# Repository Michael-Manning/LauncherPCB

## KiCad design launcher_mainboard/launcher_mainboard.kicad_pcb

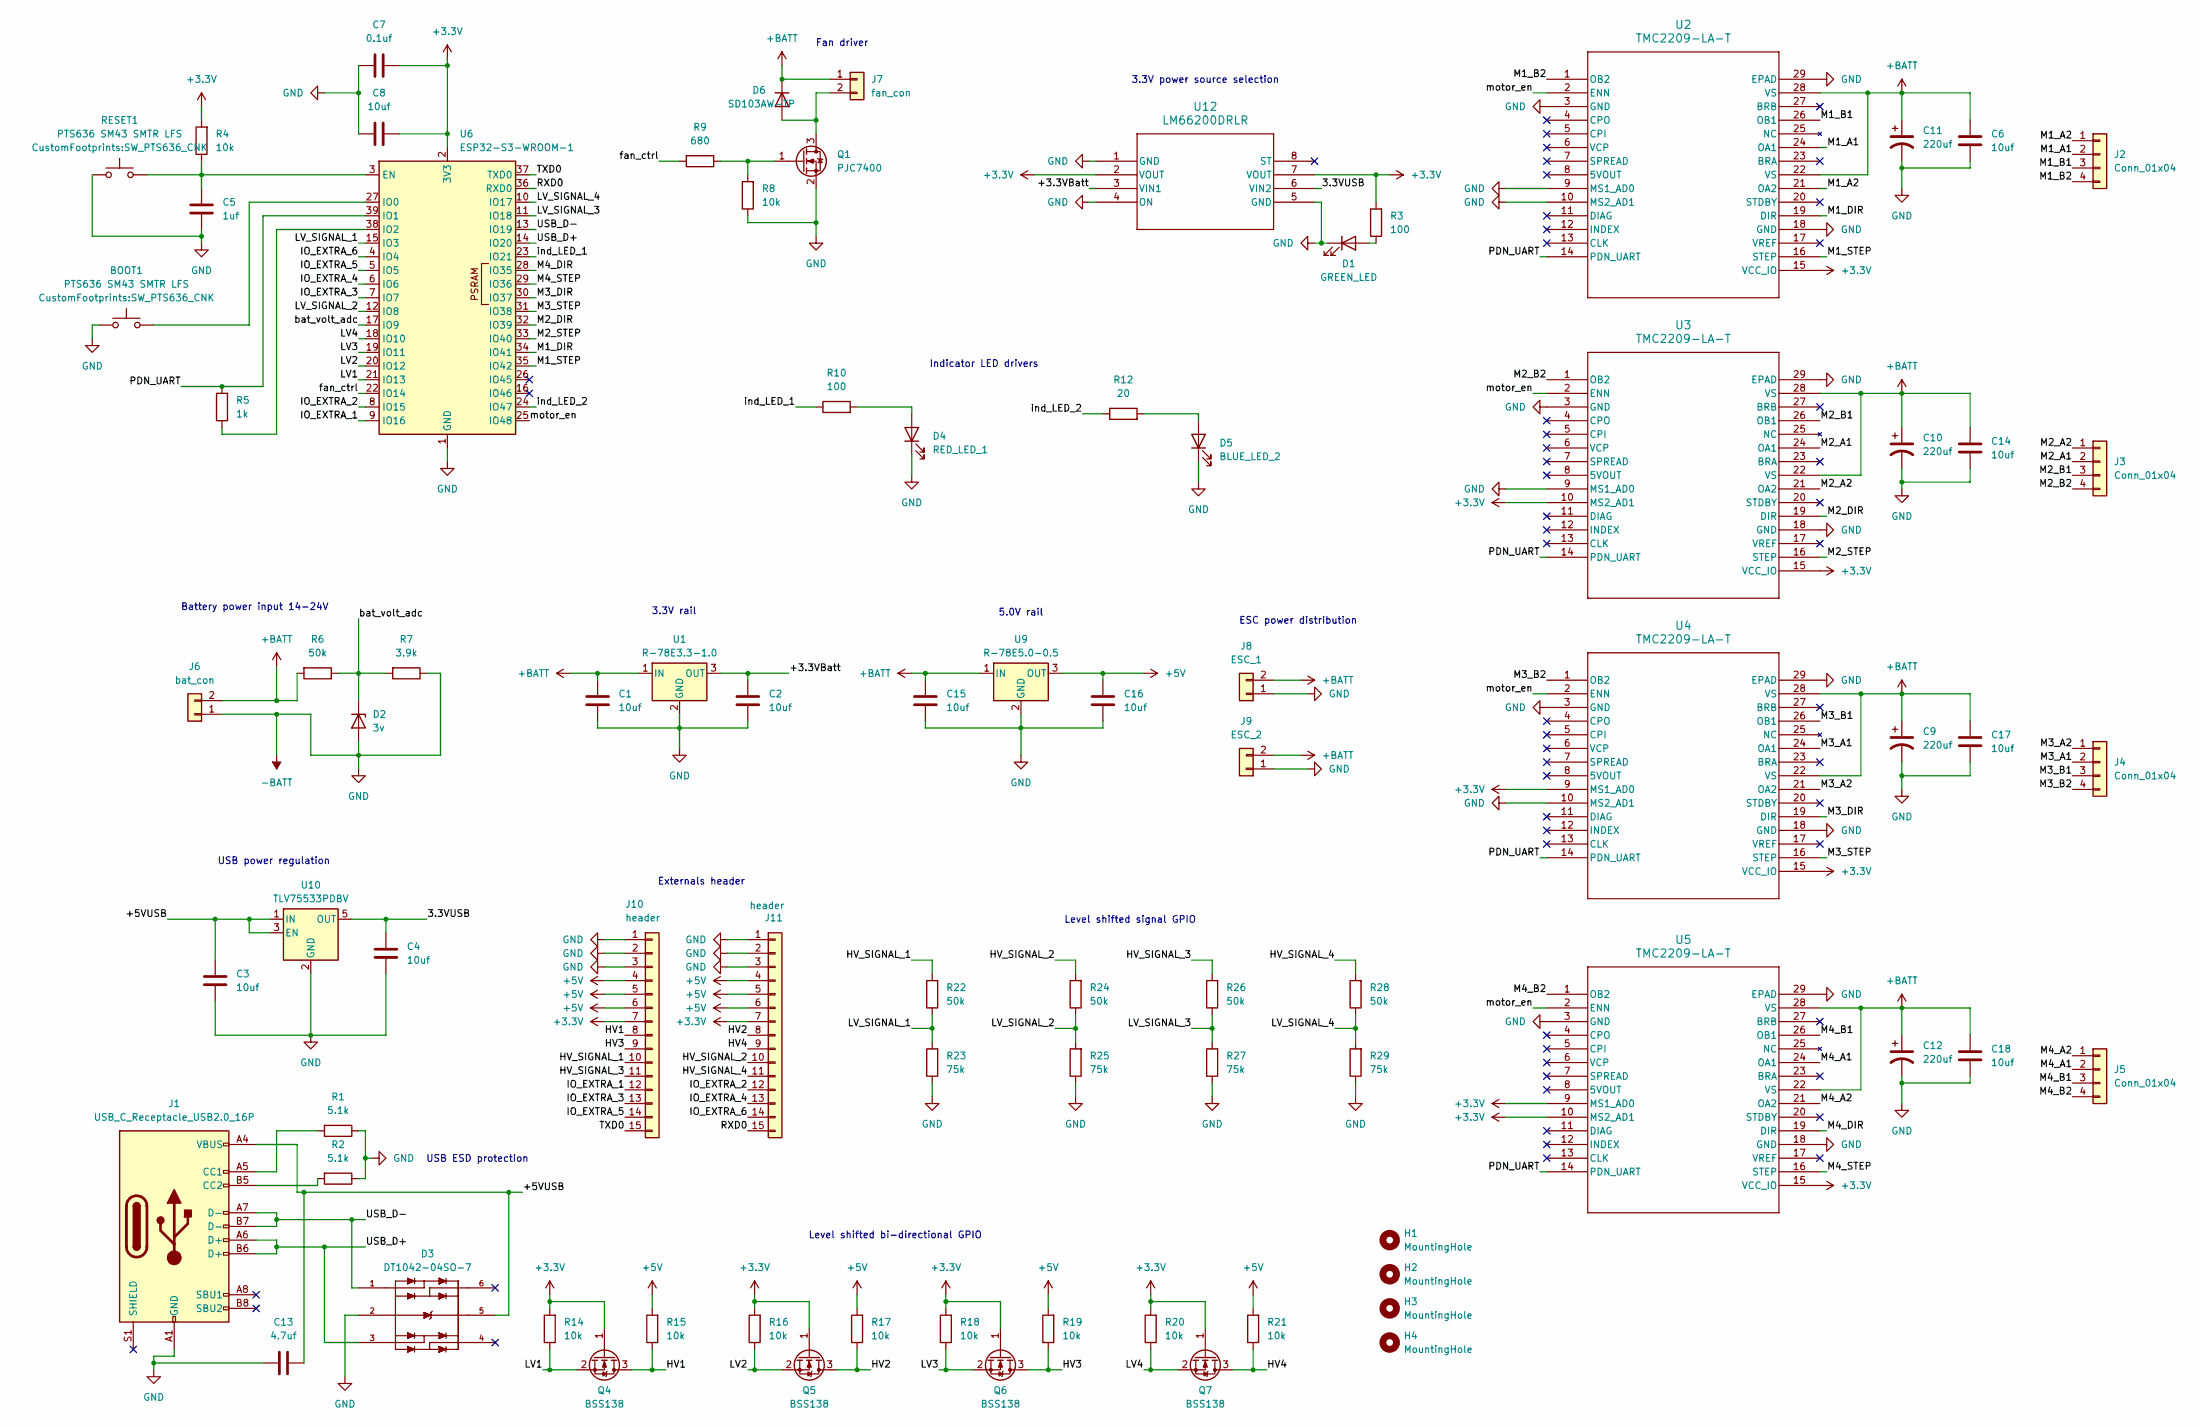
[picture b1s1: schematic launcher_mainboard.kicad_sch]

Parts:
BOOT1: PTS636 SM43 SMTR LFS; SW_PTS636_CNK
C1, C2, C3, C4, C6, C8, C14, C15, C16, C17, C18: 10uf; C_0805_2012Metric
C5: 1uf; C_0805_2012Metric
C7: 0.1uf; C_0805_2012Metric
C9, C10, C11, C12: 220uf; CP_Elec_8x6.7
C13: 4.7uf; C_0805_2012Metric
D1: GREEN_LED; LED_0805_2012Metric
D2: 3v; D_SOD-123
D3: DT1042-04SO-7; SOT95P285X140-6N; PARTREV 2-2
D4: RED_LED_1; LED_0805_2012Metric
D5: BLUE_LED_2; LED_0805_2012Metric
D6: SD103AW-TP; D_SOD-123
H1, H2, H3, H4: MountingHole; MountingHole_3.2mm_M3_Pad_TopBottom
J1: USB_C_Receptacle_USB2.0_16P; USB_C_Receptacle_GCT_USB4105-xx-A_16P_TopMnt_Horizontal
J2, J3, J4, J5: Conn_01x04; JST_XH_B4B-XH-A_1x04_P2.50mm_Vertical
J6: bat_con; AMASS_XT60-M_1x02_P7.20mm_Vertical
J7: fan_con; JST_XH_B2B-XH-A_1x02_P2.50mm_Vertical
J8: ESC_1; AMASS_XT60-F_1x02_P7.20mm_Vertical
J9: ESC_2; AMASS_XT60-F_1x02_P7.20mm_Vertical
J10, J11: header; PinHeader_1x15_P2.54mm_Vertical
Q1: PJC7400; SOT-323_SC-70
Q4, Q5, Q6, Q7: BSS138; SOT-23
R1, R2: 5.1k; R_0805_2012Metric
R3, R10: 100; R_0805_2012Metric
R4, R8, R14, R15, R16, R17, R18, R19, R20, R21: 10k; R_0805_2012Metric
R5: 1k; R_0805_2012Metric
R6, R22, R24, R26, R28: 50k; R_0805_2012Metric
R7: 3.9k; R_0805_2012Metric
R9: 680; R_0805_2012Metric
R12: 20; R_0805_2012Metric
R23, R25, R27, R29: 75k; R_0805_2012Metric
RESET1: PTS636 SM43 SMTR LFS; SW_PTS636_CNK
U1: R-78E3.3-1.0; Converter_DCDC_RECOM_R-78E-0.5_THT
U2, U3, U4, U5: TMC2209-LA-T; TCM2209_Module
U6: ESP32-S3-WROOM-1
U9: R-78E5.0-0.5; Converter_DCDC_RECOM_R-78E-0.5_THT
U10: TLV75533PDBV; SOT-23-5
U12: LM66200DRLR; SOT-5X3_DRL_TEX

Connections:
+3.3V: C7.2, C8.2, J10.7, J11.7, Q4.1 (G), Q5.1 (G), Q6.1 (G), Q7.1 (G), R3.2, R4.2, R14.2, R16.2, R18.2, R20.2, U2.15 (VCC_IO), U3.10 (MS2_AD1), U3.15 (VCC_IO), U4.9 (MS1_AD0), U4.15 (VCC_IO), U5.9 (MS1_AD0), U5.10 (MS2_AD1), U5.15 (VCC_IO), U6.2 (3V3), U12.2 (VOUT), U12.7 (VOUT)
+5V: C16.1, J10.4, J10.5, J10.6, J11.4, J11.5, J11.6, R15.2, R17.2, R19.2, R21.2, U9.3 (OUT)
+BATT: C1.1, C6.1, C9.1, C10.1, C11.1, C12.1, C14.1, C15.1, C17.2, C18.2, D6.1 (K), J6.2, J7.1, J8.2, J9.2, R6.2, U1.1 (IN), U2.22 (VS), U2.28 (VS), U3.22 (VS), U3.28 (VS), U4.22 (VS), U4.28 (VS), U5.22 (VS), U5.28 (VS), U9.1 (IN)
-BATT: BOOT1.1, C1.2, C2.2, C3.2, C4.2, C5.2, C6.2, C7.1, C8.1, C9.2, C10.2, C11.2, C12.2, C13.2, C14.2, C15.2, C16.2, C17.1, C18.1, D1.1 (K), D2.2 (A), D3.2, D4.1 (K), D5.1 (K), J1.A1 (GND), J1.A12 (GND), J1.B1 (GND), J1.B12 (GND), J6.1, J8.1, J9.1, J10.1, J10.2, J10.3, J11.1, J11.2, J11.3, Q1.2 (S), R1.1, R2.1, R7.1, R8.1, R23.1, R25.1, R27.1, R29.1, RESET1.1, U1.2 (GND), U2.3 (GND), U2.9 (MS1_AD0), U2.10 (MS2_AD1), U2.18 (GND), U2.29 (EPAD), U3.3 (GND), U3.9 (MS1_AD0), U3.18 (GND), U3.29 (EPAD), U4.3 (GND), U4.10 (MS2_AD1), U4.18 (GND), U4.29 (EPAD), U5.3 (GND), U5.18 (GND), U5.29 (EPAD), U6.1 (GND), U6.40 (GND), U6.41 (GND), U9.2 (GND), U10.2 (GND), U12.1 (GND), U12.4 (ON), U12.5 (GND)
/3.3VUSB: C4.1, U10.5 (OUT), U12.6 (VIN2)
/+3.3VBatt: C2.1, U1.3 (OUT), U12.3 (VIN1)
/+5VUSB: C3.1, C13.1, D3.5, J1.A4 (VBUS), J1.A9 (VBUS), J1.B4 (VBUS), J1.B9 (VBUS), U10.1 (IN), U10.3 (EN)
/HV1: J10.8, Q4.3 (D), R15.1
/HV2: J11.8, Q5.3 (D), R17.1
/HV3: J10.9, Q6.3 (D), R19.1
/HV4: J11.9, Q7.3 (D), R21.1
/HV_SIGNAL_1: J10.10, R22.2
/HV_SIGNAL_2: J11.10, R24.2
/HV_SIGNAL_3: J10.11, R26.2
/HV_SIGNAL_4: J11.11, R28.2
/IO_EXTRA_1: J10.12, U6.9 (IO16)
/IO_EXTRA_2: J11.12, U6.8 (IO15)
/IO_EXTRA_3: J10.13, U6.7 (IO7)
/IO_EXTRA_4: J11.13, U6.6 (IO6)
/IO_EXTRA_5: J10.14, U6.5 (IO5)
/IO_EXTRA_6: J11.14, U6.4 (IO4)
/LV1: Q4.2 (S), R14.1, U6.21 (IO13)
/LV2: Q5.2 (S), R16.1, U6.20 (IO12)
/LV3: Q6.2 (S), R18.1, U6.19 (IO11)
/LV4: Q7.2 (S), R20.1, U6.18 (IO10)
/LV_SIGNAL_1: R22.1, R23.2, U6.15 (IO3)
/LV_SIGNAL_2: R24.1, R25.2, U6.12 (IO8)
/LV_SIGNAL_3: R26.1, R27.2, U6.11 (IO18)
/LV_SIGNAL_4: R28.1, R29.2, U6.10 (IO17)
/M1_A1: J2.2, U2.24 (OA1)
/M1_A2: J2.1, U2.21 (OA2)
/M1_B1: J2.3, U2.26 (OB1)
/M1_B2: J2.4, U2.1 (OB2)
/M1_DIR: U2.19 (DIR), U6.34 (IO41)
/M1_STEP: U2.16 (STEP), U6.35 (IO42)
/M2_A1: J3.2, U3.24 (OA1)
/M2_A2: J3.1, U3.21 (OA2)
/M2_B1: J3.3, U3.26 (OB1)
/M2_B2: J3.4, U3.1 (OB2)
/M2_DIR: U3.19 (DIR), U6.32 (IO39)
/M2_STEP: U3.16 (STEP), U6.33 (IO40)
/M3_A1: J4.2, U4.24 (OA1)
/M3_A2: J4.1, U4.21 (OA2)
/M3_B1: J4.3, U4.26 (OB1)
/M3_B2: J4.4, U4.1 (OB2)
/M3_DIR: U4.19 (DIR), U6.30 (IO37)
/M3_STEP: U4.16 (STEP), U6.31 (IO38)
/M4_A1: J5.2, U5.24 (OA1)
/M4_A2: J5.1, U5.21 (OA2)
/M4_B1: J5.3, U5.26 (OB1)
/M4_B2: J5.4, U5.1 (OB2)
/M4_DIR: U5.19 (DIR), U6.28 (IO35)
/M4_STEP: U5.16 (STEP), U6.29 (IO36)
/PDN_UART: R5.2, U2.14 (PDN_UART), U3.14 (PDN_UART), U4.14 (PDN_UART), U5.14 (PDN_UART), U6.39 (IO1)
/RXD0: J11.15, U6.36 (RXD0)
/TXD0: J10.15, U6.37 (TXD0)
/USB_D+: D3.3, J1.A6 (D+), J1.B6 (D+), U6.14 (IO20)
/USB_D-: D3.1, J1.A7 (D-), J1.B7 (D-), U6.13 (IO19)
/bat_volt_adc: D2.1 (K), R6.1, R7.2, U6.17 (IO9)
/fan_ctrl: R9.2, U6.22 (IO14)
/ind_LED_1: R10.1, U6.23 (IO21)
/ind_LED_2: R12.1, U6.24 (IO47)
/motor_en: U2.2 (ENN), U3.2 (ENN), U4.2 (ENN), U5.2 (ENN), U6.25 (IO48)
unnamed: D1.2 (A), R3.1
unnamed: D4.2 (A), R10.2
unnamed: D5.2 (A), R12.2
unnamed: D6.2 (A), J7.2, Q1.3 (D)
unnamed: J1.A5 (CC1), R1.2
unnamed: J1.B5 (CC2), R2.2
unnamed: Q1.1 (G), R8.2, R9.1
unnamed: C5.1, R4.1, RESET1.2, U6.3 (EN)
unnamed: BOOT1.2, U6.27 (IO0)
unnamed: R5.1, U6.38 (IO2)

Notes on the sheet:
3.3V power source selection
3.3V rail
Fan driver
ESC power distribution
USB ESD protection
Level shifted signal GPIO
Indicator LED drivers
5.0V rail
Level shifted bi-directional GPIO
Battery power input 14-24V
Externals header
USB power regulation

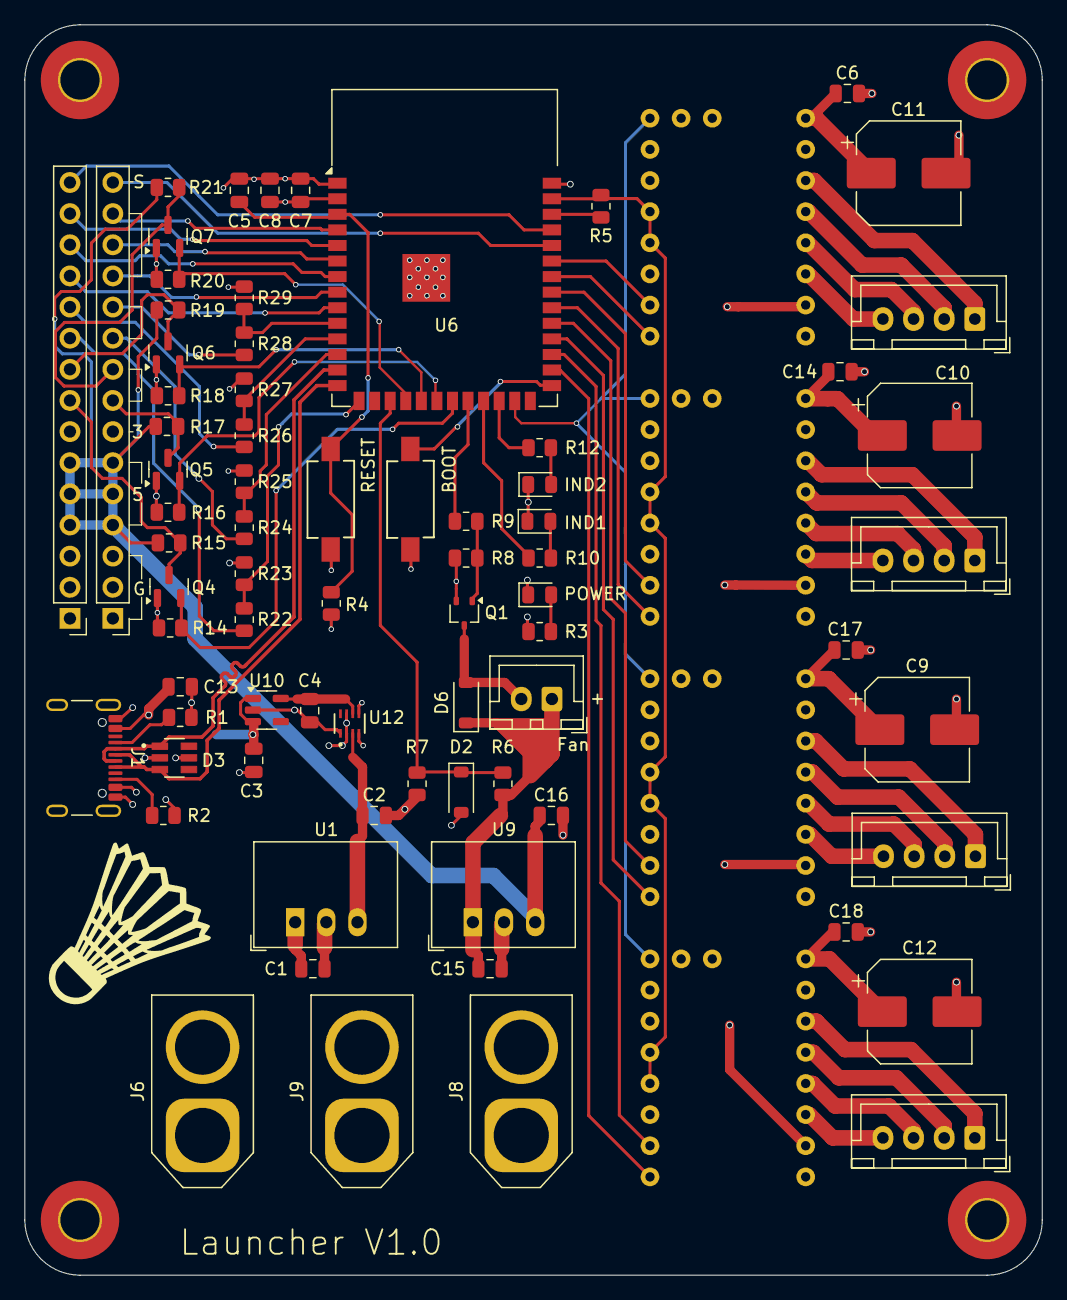
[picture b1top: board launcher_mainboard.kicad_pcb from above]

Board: 4 copper layers, 83.0 x 102.0 mm, 83 parts (0 on the bottom side), 73 nets.

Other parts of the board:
.: LOGO; birdie_img

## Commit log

2024-03-26 battery voltage adc divider
2024-03-27 more electricity
2024-03-27 uhhh
2024-03-28 ellectt elelecitfy
2024-03-28 power selector, moved some files
2024-03-31 first complete scematic draft
2024-03-31 added more footprints. Rought layout
2024-04-01 more layout
2024-04-03 project restructure, switched out EDC IC, more layout
2024-04-04 renamed folder. How do differential pairs work?
2024-04-04 more routing
2024-04-05 fixed switch footprint
2024-04-07 pre usb change
2024-04-08 switched to SMD USB C connector
2024-04-08 increased via sizes
2024-04-08 design rule fixes
2024-04-08 shifted headers away from board edge
2024-04-08 added missing models
2024-04-08 removed lock files
2024-04-08 shifted over some resisters
2024-04-09 notes
2024-04-10 switch stepper connector to XH
2024-04-11 flipped ESD IC, selected zener diode and updated footprint
2024-04-12 finished up diode stuff
2024-04-14 ordered board
